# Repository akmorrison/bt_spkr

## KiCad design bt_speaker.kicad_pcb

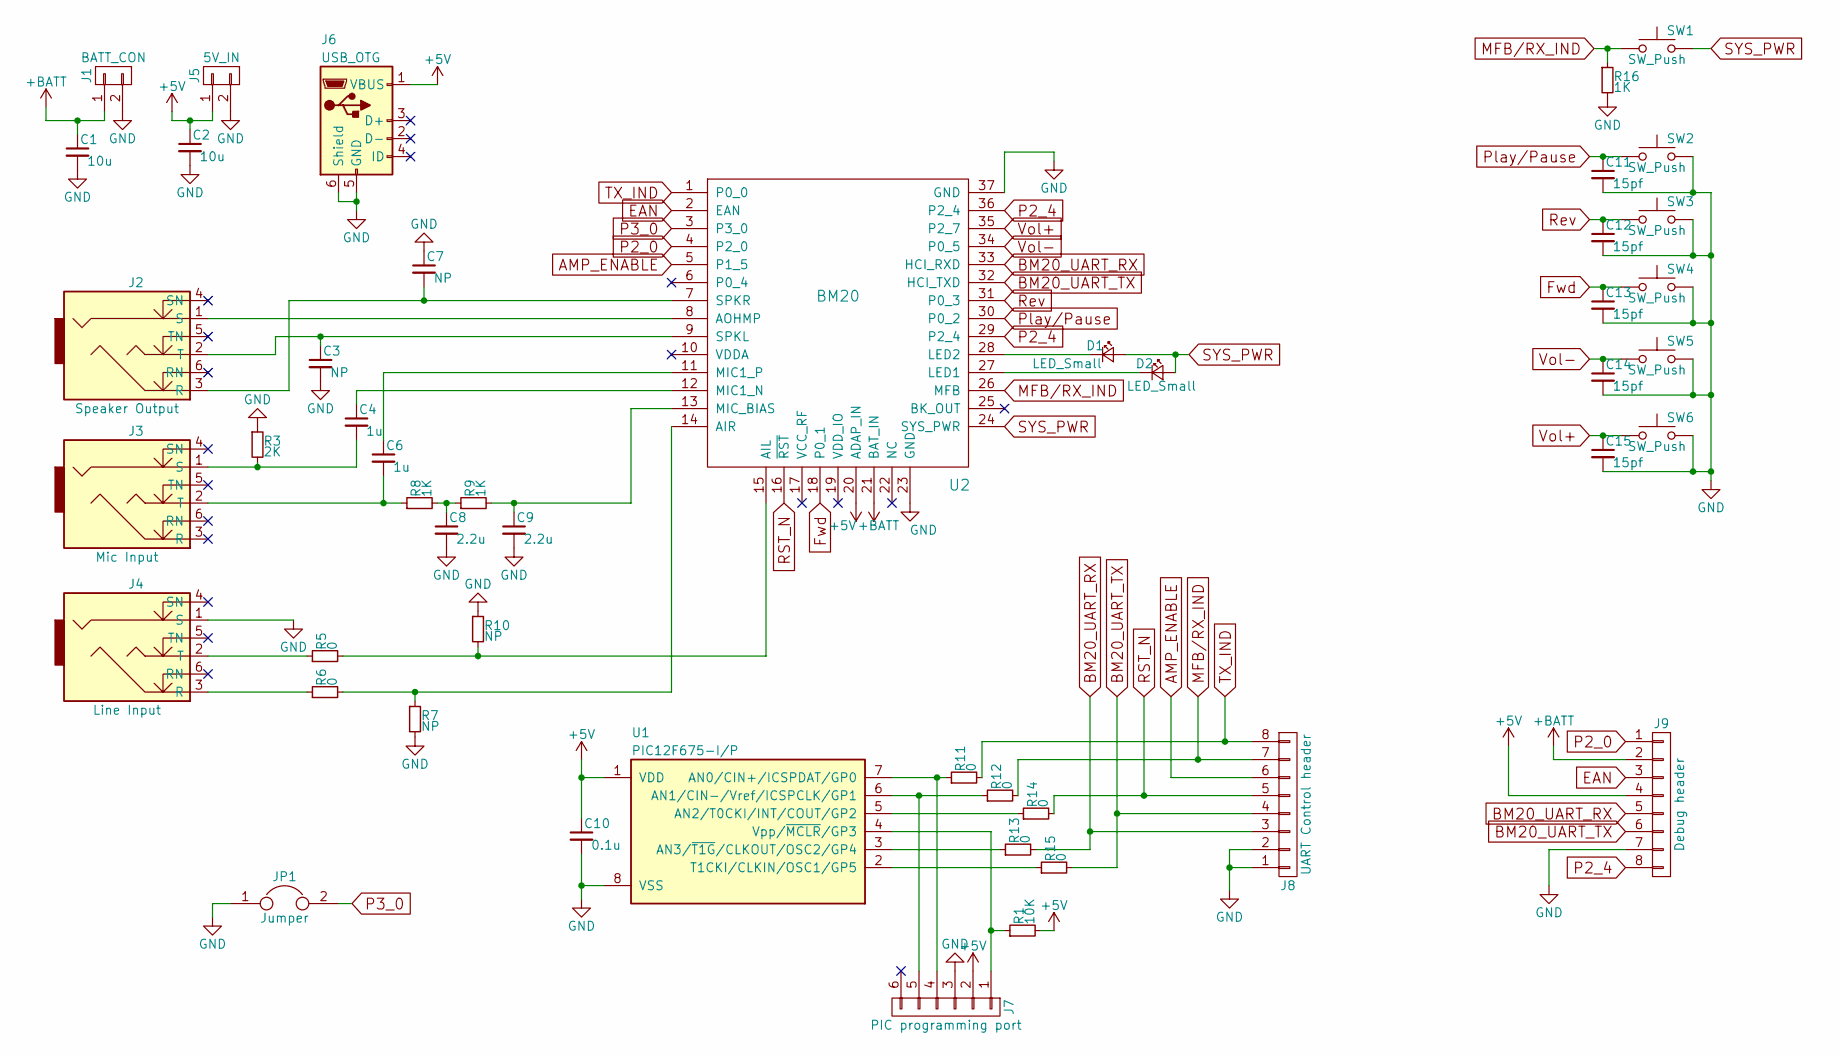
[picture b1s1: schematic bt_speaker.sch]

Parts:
C1, C2: 10u; C_0805_HandSoldering
C3, C7: NP; C_0805_HandSoldering
C4, C6: 1u; C_0805_HandSoldering
C8, C9: 2.2u; C_0805_HandSoldering
C10: 0.1u; C_0805_HandSoldering
C11, C12, C13, C14, C15: 15pf; C_0805_HandSoldering
D1, D2: LED_Small; LED_1206_HandSoldering
J1: BATT_CON; Socket_Strip_Straight_1x02_Pitch2.54mm
J2: Speaker Output; SJ1-3525N
J3: Mic Input; SJ1-3525N
J4: Line Input; SJ1-3525N
J5: 5V_IN; Socket_Strip_Straight_1x02_Pitch2.54mm
J6: USB_OTG; USB_Micro-B
J7: PIC programming port; Socket_Strip_Straight_1x06_Pitch2.54mm
J8: UART Control header; Socket_Strip_Straight_1x08_Pitch2.54mm
J9: Debug header; Socket_Strip_Straight_1x08_Pitch2.54mm
JP1: Jumper; Pin_Header_Straight_1x02_Pitch2.54mm
R1: 10K; R_0805_HandSoldering
R3: 2K; R_0805_HandSoldering
R5, R6, R11, R12, R13, R14, R15: 0; R_0805_HandSoldering
R7, R10: NP; R_0805_HandSoldering
R8, R9, R16: 1K; R_0805_HandSoldering
SW1, SW2, SW3, SW4, SW5, SW6: SW_Push; SW_SPST_B3SL-1002P
U1: PIC12F675-I/P; DIP-8_W7.62mm_Socket
U2: BM20

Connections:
+5V: C2.1, C10.1, J5.1, J6.1 (VBUS), J7.2, J9.4, R1.2, U1.1 (VDD), U2.20 (ADAP_IN)
+BATT: C1.1, J1.1, J9.2, U2.21 (BAT_IN)
AMP_ENABLE: J8.6, U2.5 (P1_5)
BM20_UART_RX: J8.3, J9.5, R13.2, U2.33 (HCI_RXD)
BM20_UART_TX: J8.4, J9.6, R15.2, U2.32 (HCI_TXD)
EAN: J9.3, U2.2 (EAN)
Fwd: C13.1, SW4.1, U2.18 (P0_1)
GND: C1.2, C2.2, C3.2, C7.1, C8.2, C9.2, C10.2, C11.2, C12.2, C13.2, C14.2, C15.2, J1.2, J4.1 (S), J5.2, J6.5 (GND), J6.6 (Shield), J7.3, J8.1, J8.2, J9.7, JP1.1, R3.1, R7.2, R10.1, R16.2, SW2.2, SW3.2, SW4.2, SW5.2, SW6.2, U1.8 (VSS), U2.23 (GND), U2.37 (GND)
MFB/RX_IND: J8.7, R12.2, R16.1, SW1.1, U2.26 (MFB)
unnamed: C3.1, J2.2 (T), U2.9 (SPKL)
unnamed: C4.1, U2.12 (MIC1_N)
unnamed: C4.2, J3.1 (S), R3.2
unnamed: C6.1, U2.11 (MIC1_P)
unnamed: C6.2, J3.2 (T), R8.1
unnamed: C7.2, J2.3 (R), U2.7 (SPKR)
unnamed: C8.1, R8.2, R9.1
unnamed: C9.1, R9.2, U2.13 (MIC_BIAS)
unnamed: D1.1 (K), U2.28 (LED2)
unnamed: D2.1 (K), U2.27 (LED1)
unnamed: J2.1 (S), U2.8 (AOHMP)
unnamed: J4.2 (T), R5.1
unnamed: J4.3 (R), R6.1
unnamed: J7.1, R1.1, U1.4 (Vpp/~MCLR~/GP3)
unnamed: J7.4, R11.1, U1.7 (AN0/CIN+/ICSPDAT/GP0)
unnamed: J7.5, R12.1, U1.6 (AN1/CIN-/Vref/ICSPCLK/GP1)
unnamed: R6.2, R7.1, U2.14 (AIR)
unnamed: R5.2, R10.2, U2.15 (AIL)
unnamed: R13.1, U1.3 (AN3/~T1G~/CLKOUT/OSC2/GP4)
unnamed: R14.1, U1.5 (AN2/T0CKI/INT/COUT/GP2)
unnamed: R15.1, U1.2 (T1CKI/CLKIN/OSC1/GP5)
P2_0: J9.1, U2.4 (P2_0)
P2_4: J9.8, U2.29 (P2_4), U2.36 (P2_4)
P3_0: JP1.2, U2.3 (P3_0)
Play/Pause: C11.1, SW2.1, U2.30 (P0_2)
RST_N: J8.5, R14.2, U2.16 (~RST~)
Rev: C12.1, SW3.1, U2.31 (P0_3)
SYS_PWR: D1.2 (A), D2.2 (A), SW1.2, U2.24 (SYS_PWR)
TX_IND: J8.8, R11.2, U2.1 (P0_0)
Vol+: C15.1, SW6.1, U2.35 (P2_7)
Vol-: C14.1, SW5.1, U2.34 (P0_5)

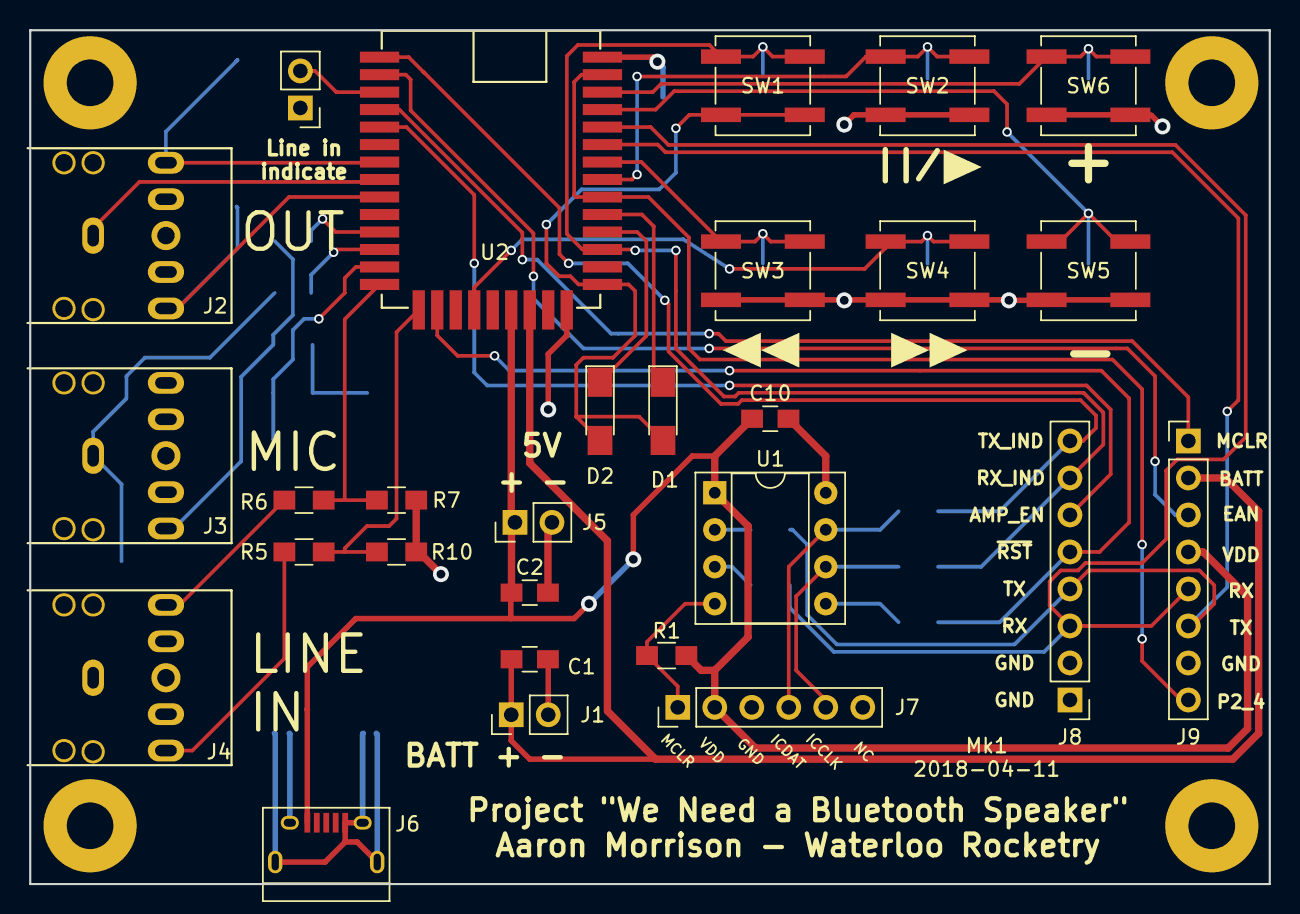
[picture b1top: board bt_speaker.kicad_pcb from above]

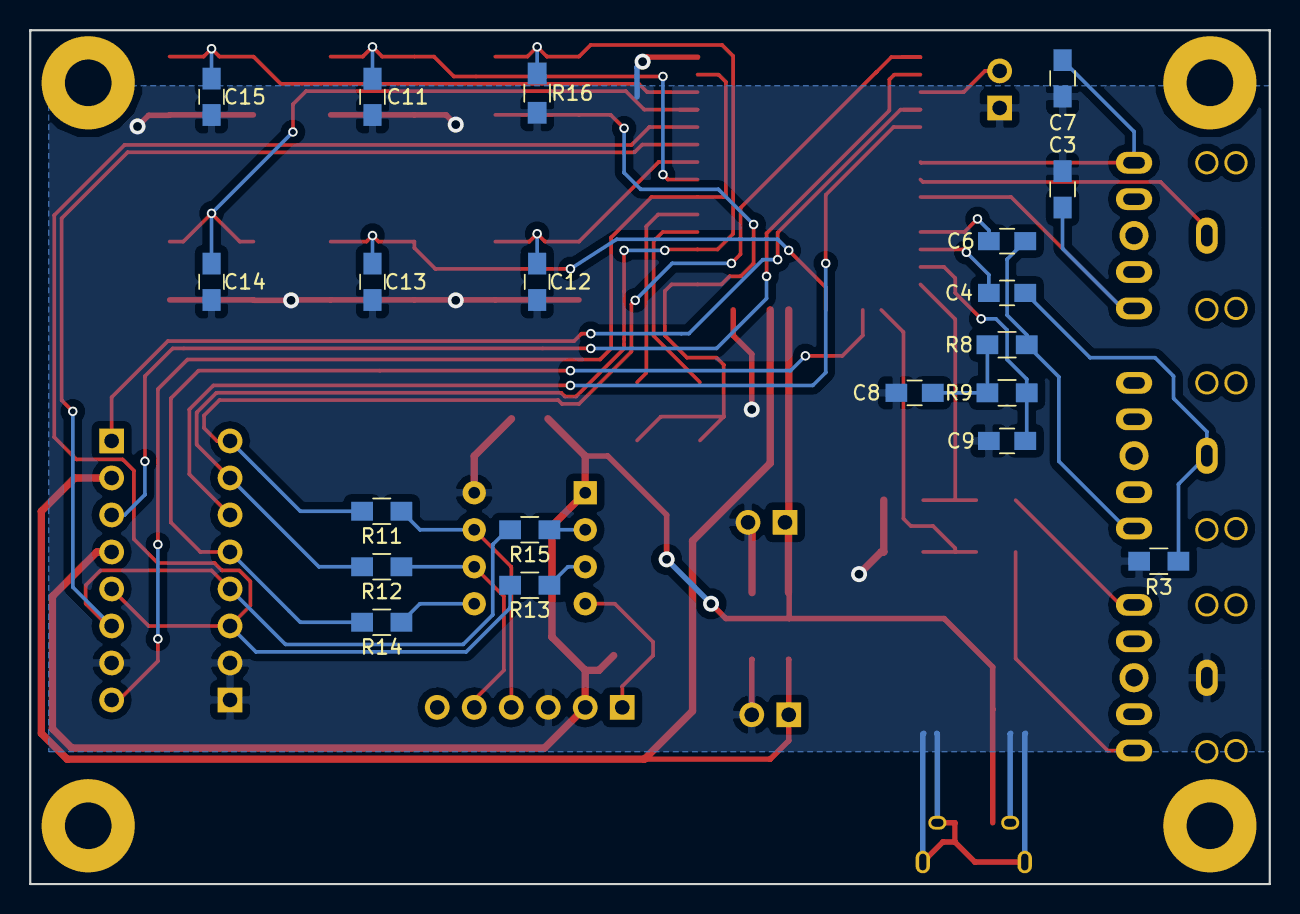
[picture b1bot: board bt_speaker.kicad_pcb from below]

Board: 2 copper layers, 85.1 x 58.6 mm, 48 parts (20 on the bottom side), 40 nets.

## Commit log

2018-07-15 Initial commit, first version of PCB
